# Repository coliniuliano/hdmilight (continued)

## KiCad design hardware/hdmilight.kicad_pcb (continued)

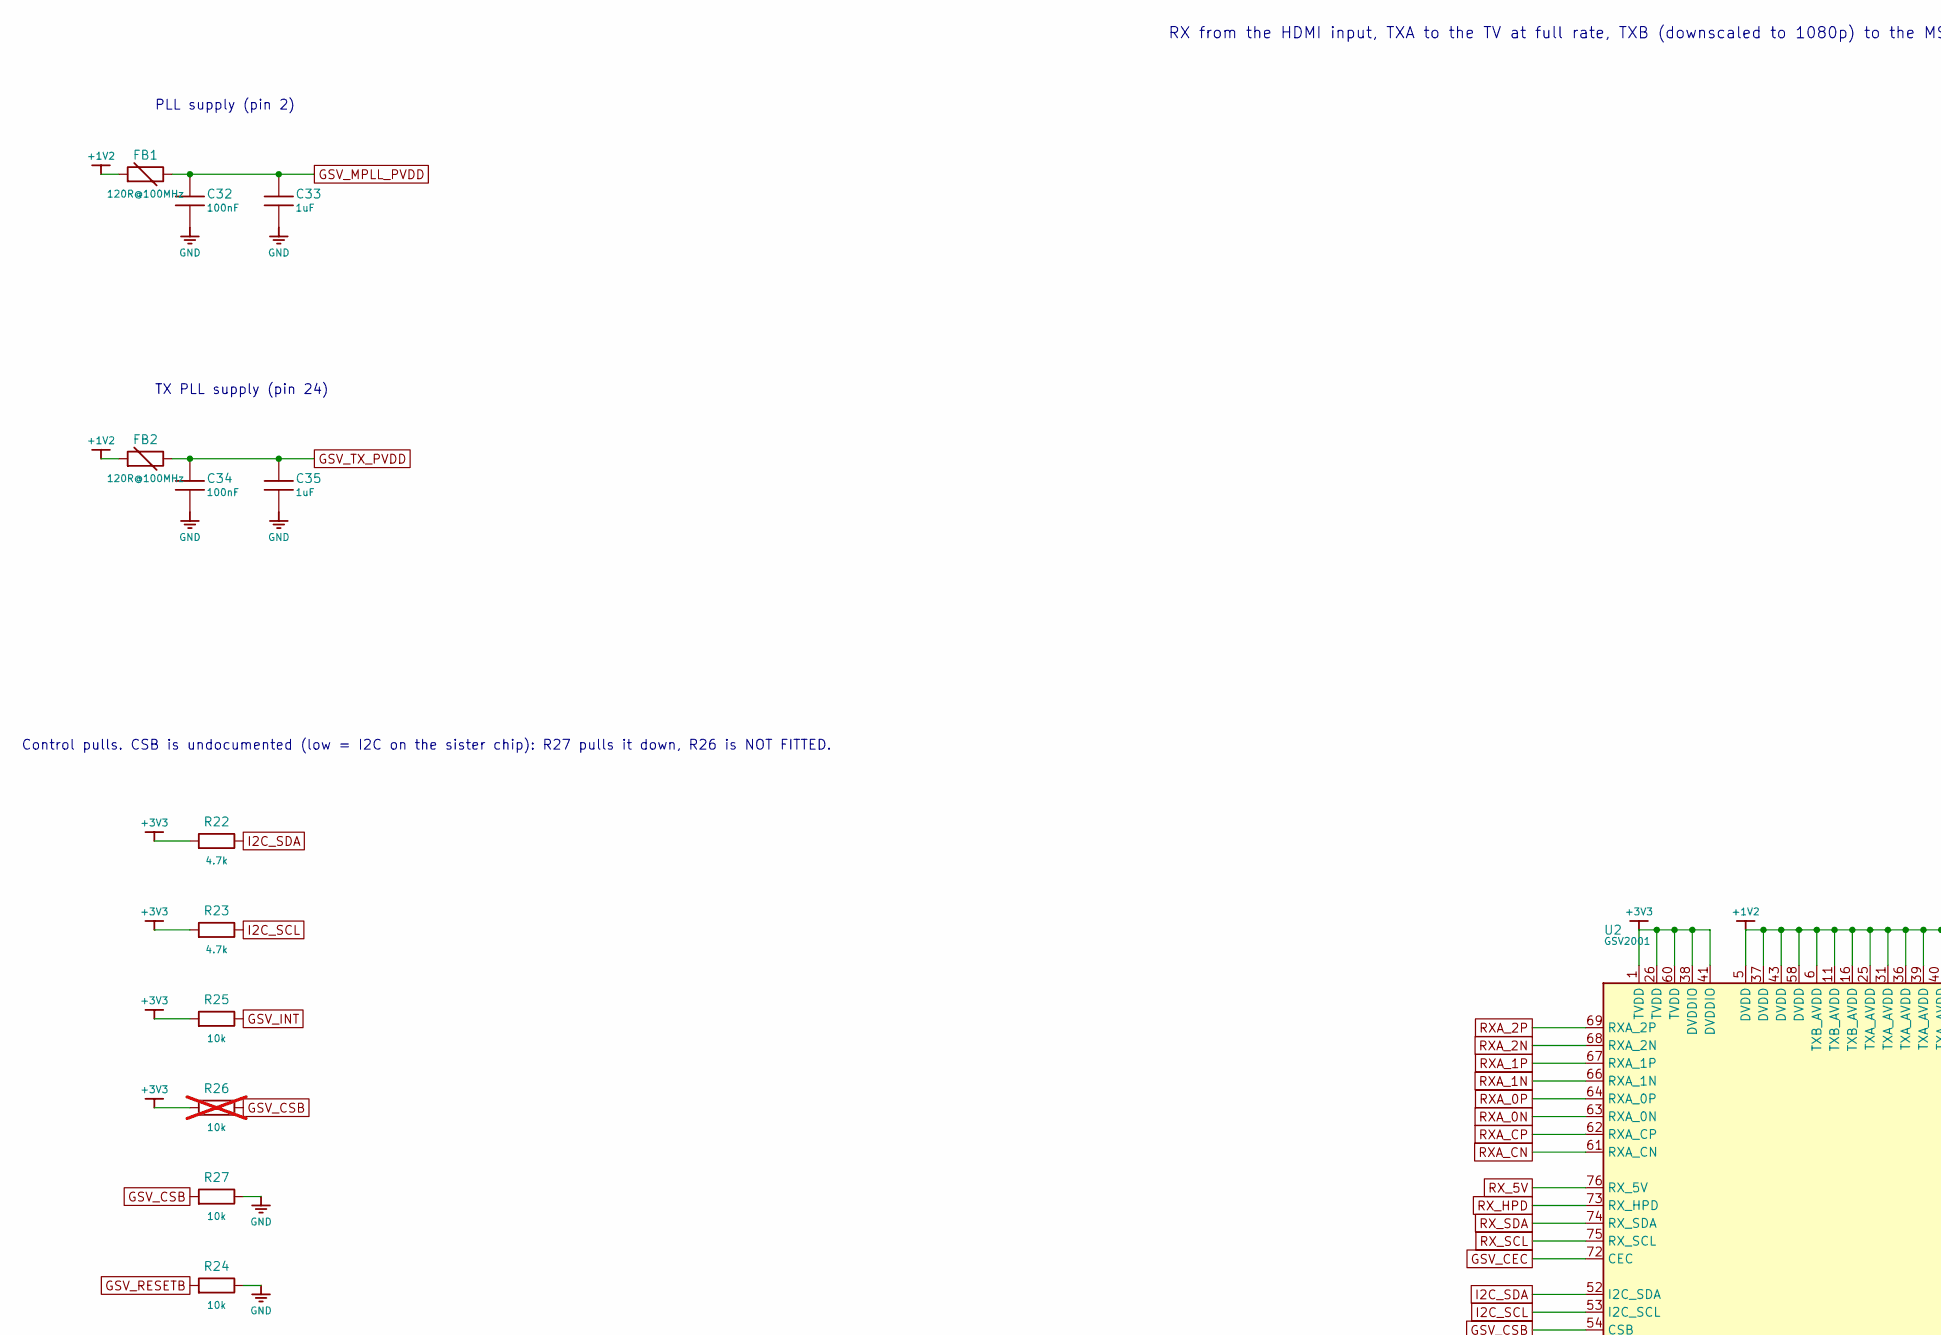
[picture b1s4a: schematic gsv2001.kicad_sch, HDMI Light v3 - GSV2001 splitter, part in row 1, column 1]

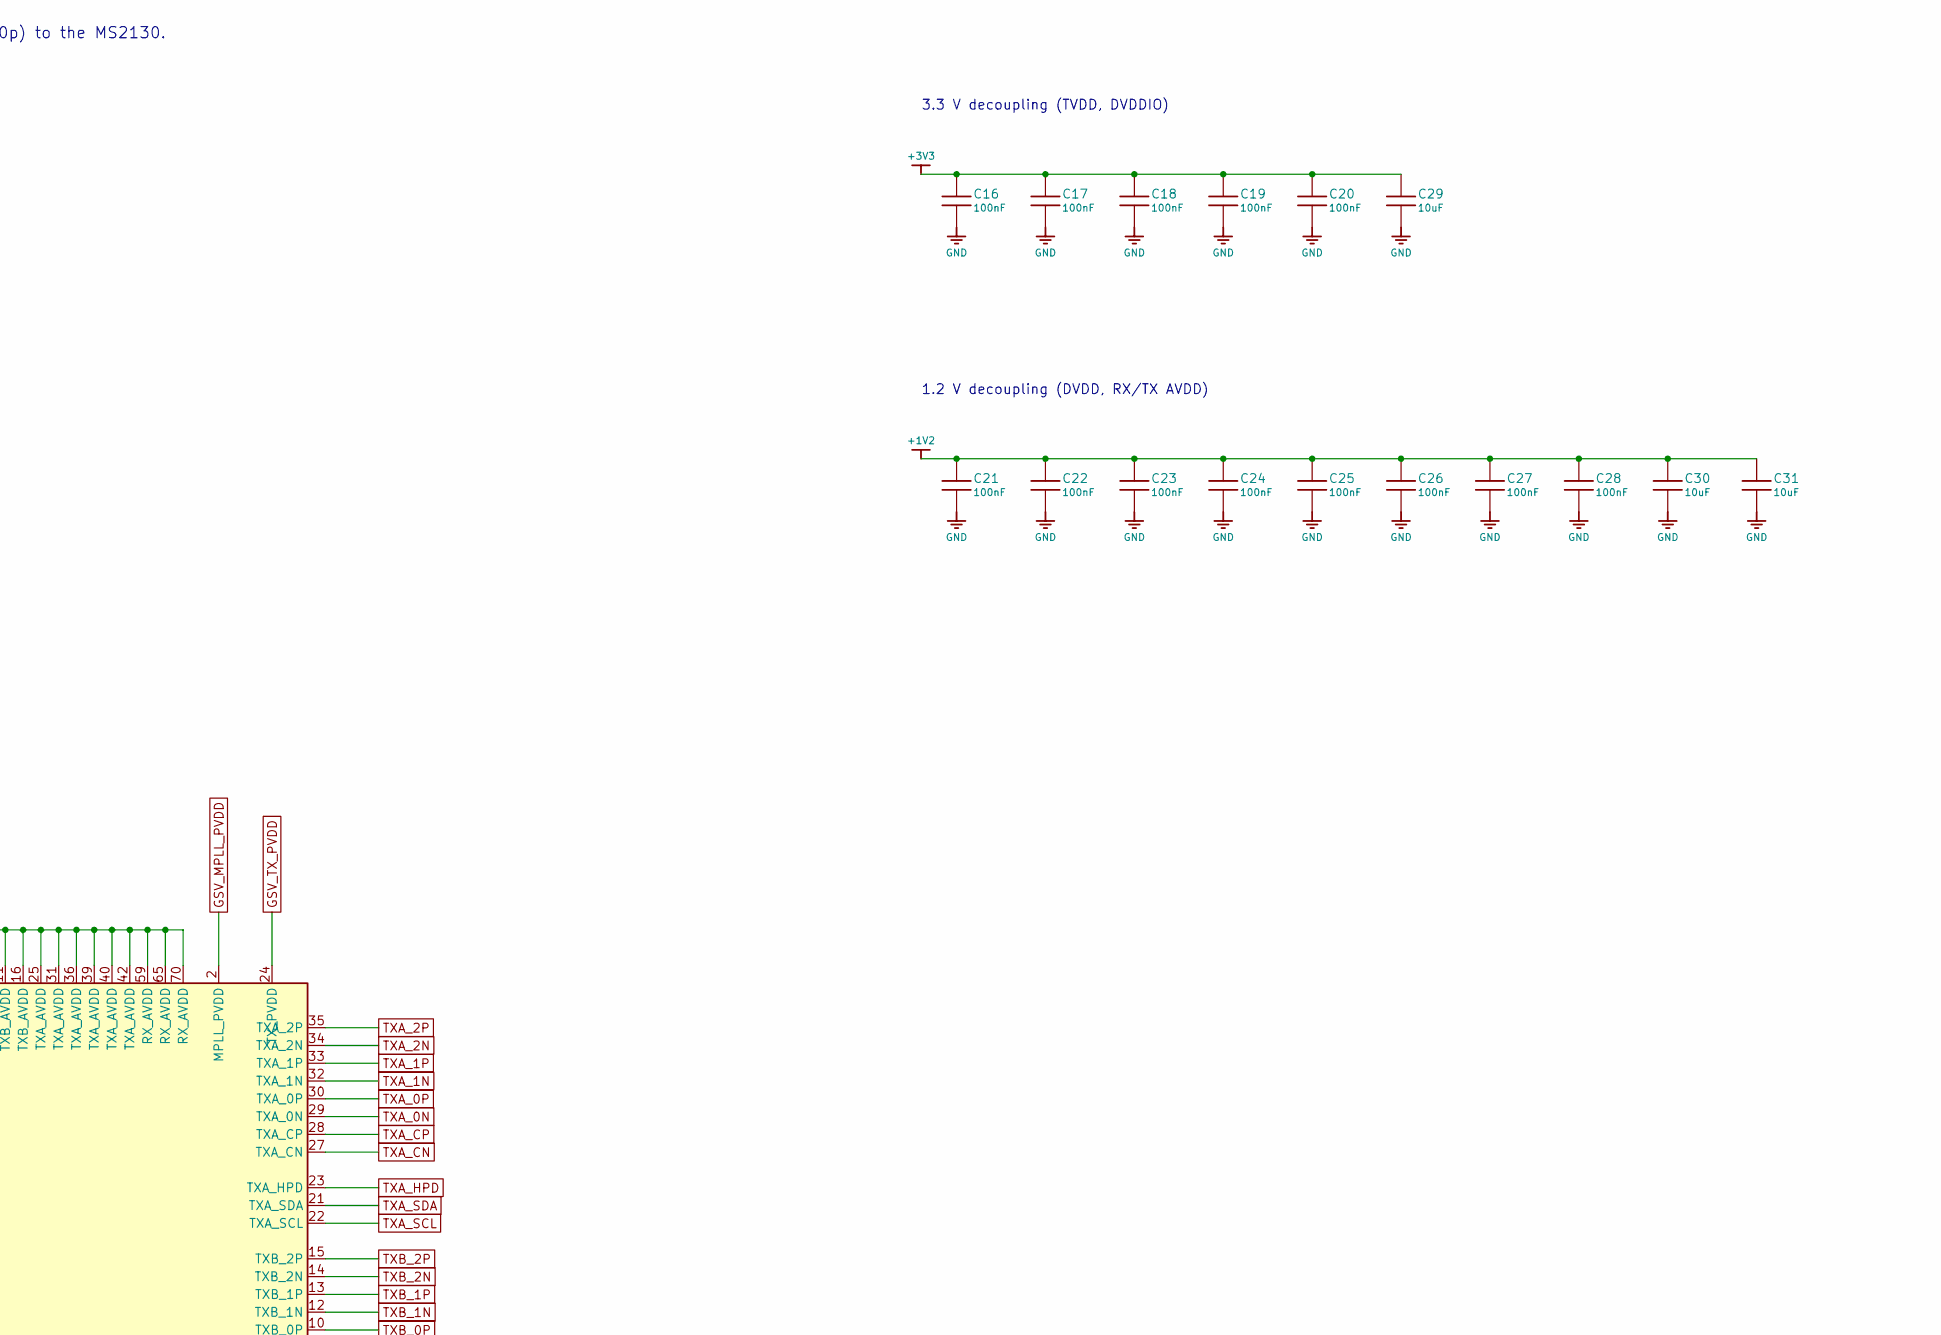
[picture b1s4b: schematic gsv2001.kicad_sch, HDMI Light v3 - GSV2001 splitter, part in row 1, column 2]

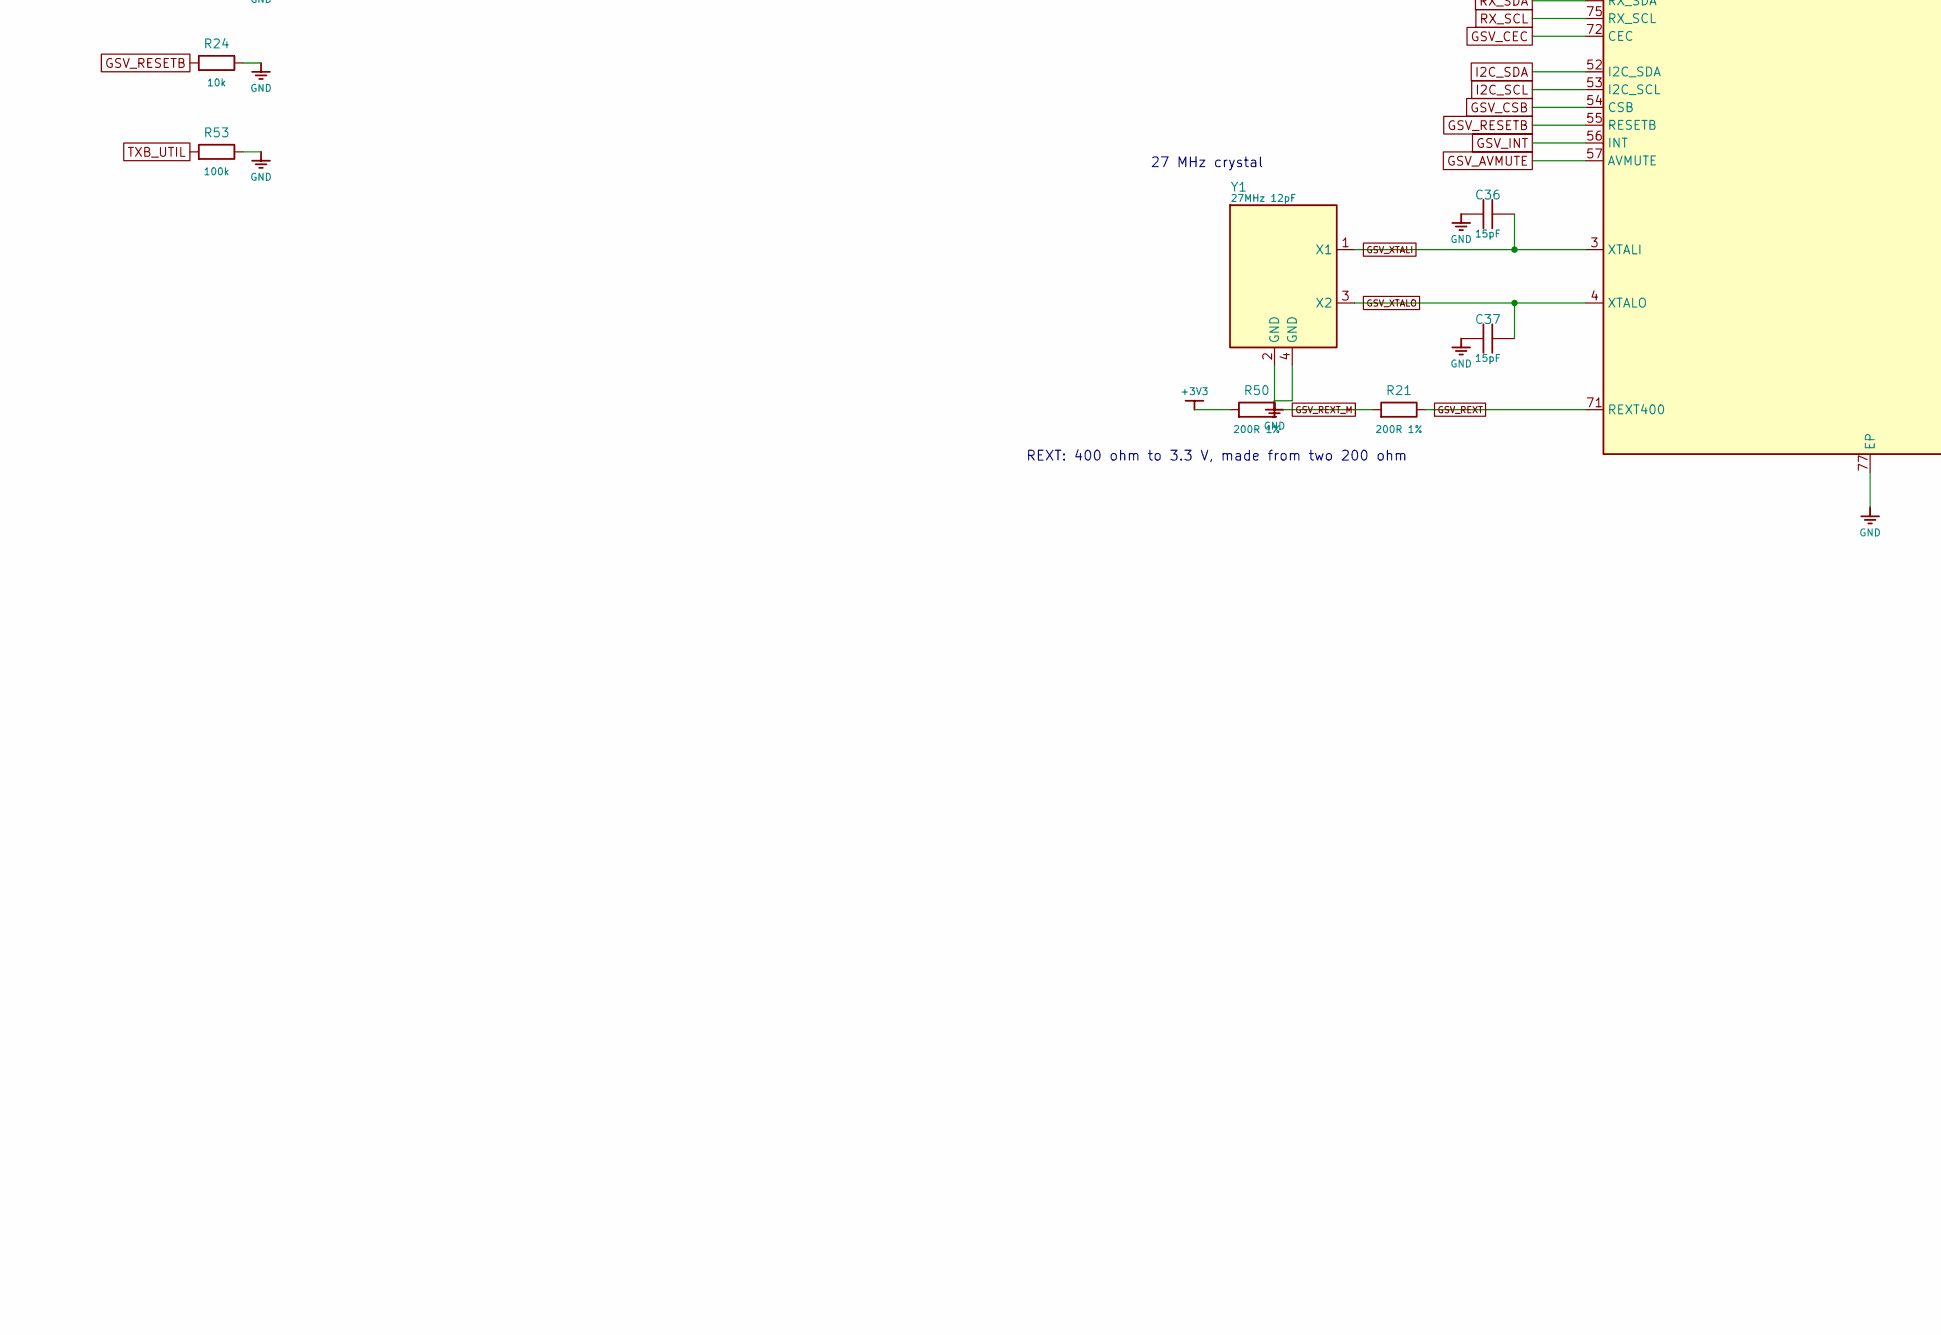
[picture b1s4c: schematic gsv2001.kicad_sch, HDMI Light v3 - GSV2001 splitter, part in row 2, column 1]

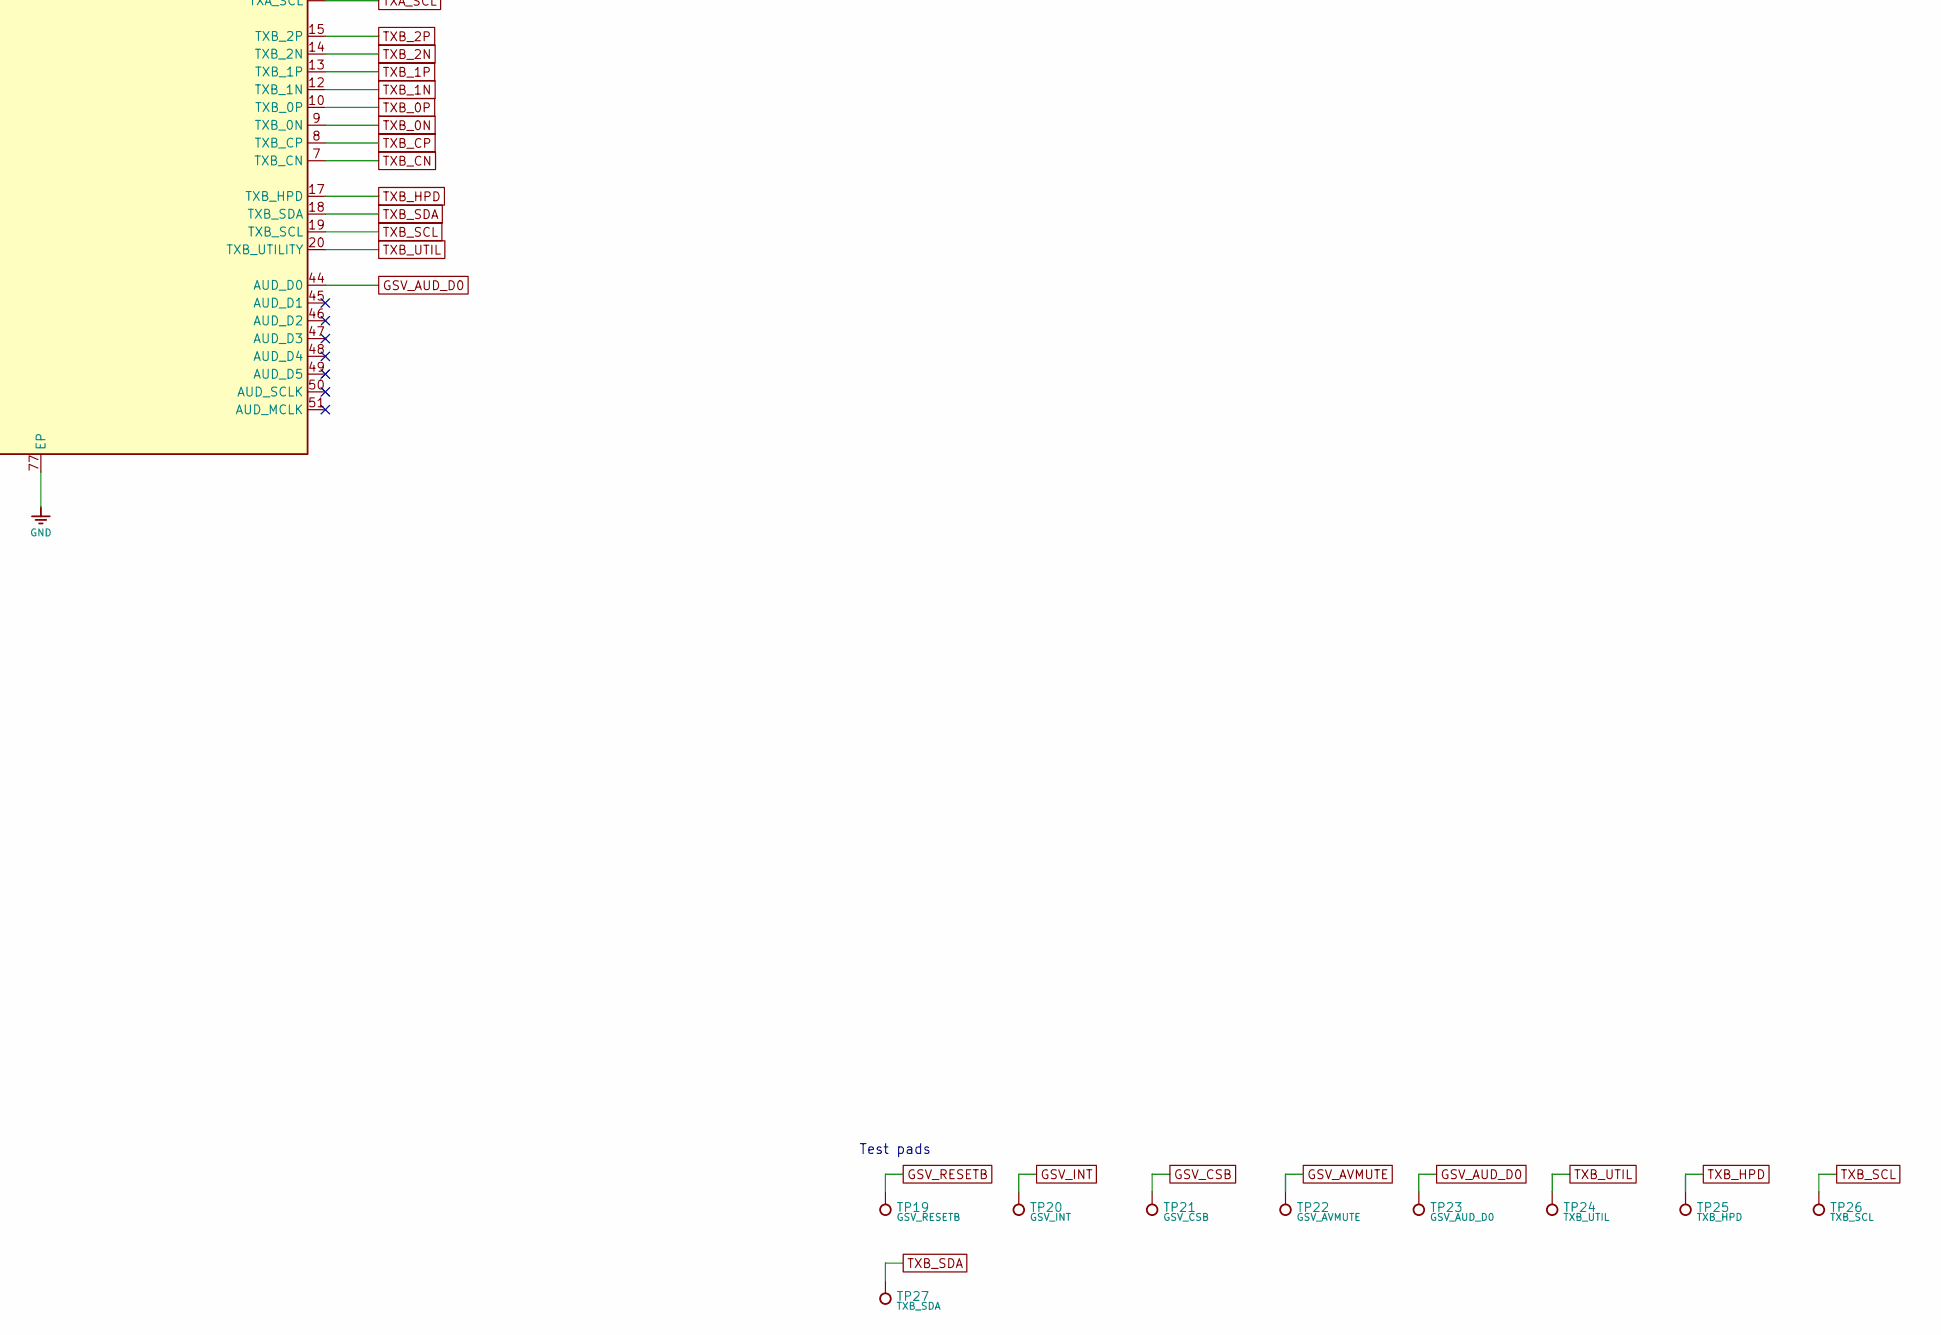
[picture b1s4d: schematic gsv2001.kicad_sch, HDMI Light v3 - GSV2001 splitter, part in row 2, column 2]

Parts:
C16, C17, C18, C19, C20, C21, C22, C23, C24, C25, C26, C27, C28, C32, C34: 100nF; C_0402_1005Metric; LCSC C1525
C29, C30, C31: 10uF; C_0603_1608Metric; LCSC C19702
C33, C35: 1uF; C_0603_1608Metric; LCSC C15849
C36, C37: 15pF; C_0402_1005Metric; LCSC C1548
FB1, FB2: 120R@100MHz; L_0603_1608Metric; MPN BLM18PG121SN1D; LCSC C14709
R21, R50: 200R 1%; R_0603_1608Metric; LCSC C8218
R22, R23: 4.7k; R_0603_1608Metric; LCSC C23162
R24, R25, R27: 10k; R_0603_1608Metric; LCSC C25804
R26: 10k; R_0603_1608Metric; LCSC C25804; not fitted
R53: 100k; R_0603_1608Metric; LCSC C25803
TP19: GSV_RESETB; TestPoint_Pad_D1.0mm
TP20: GSV_INT; TestPoint_Pad_D1.0mm
TP21: GSV_CSB; TestPoint_Pad_D1.0mm
TP22: GSV_AVMUTE; TestPoint_Pad_D1.0mm
TP23: GSV_AUD_D0; TestPoint_Pad_D1.0mm
TP24: TXB_UTIL; TestPoint_Pad_D1.0mm
TP25: TXB_HPD; TestPoint_Pad_D1.0mm
TP26: TXB_SCL; TestPoint_Pad_D1.0mm
TP27: TXB_SDA; TestPoint_Pad_D1.0mm
U2: GSV2001; QFN-76-1EP_9x9mm_P0.4mm_EP6.3x6.3mm; MPN GSV2001
Y1: 27MHz 12pF; Crystal_SMD_3225-4Pin_3.2x2.5mm; MPN X322527MOB4SI; LCSC C70595

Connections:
+1V2: C21.1, C22.1, C23.1, C24.1, C25.1, C26.1, C27.1, C28.1, C30.1, C31.1, FB1.1, FB2.1, U2.5 (DVDD), U2.6 (TXB_AVDD), U2.11 (TXB_AVDD), U2.16 (TXB_AVDD), U2.25 (TXA_AVDD), U2.31 (TXA_AVDD), U2.36 (TXA_AVDD), U2.37 (DVDD), U2.39 (TXA_AVDD), U2.40 (TXA_AVDD), U2.42 (TXA_AVDD), U2.43 (DVDD), U2.58 (DVDD), U2.59 (RX_AVDD), U2.65 (RX_AVDD), U2.70 (RX_AVDD); also elsewhere on the board
+3V3: C16.1, C17.1, C18.1, C19.1, C20.1, C29.1, R22.1, R23.1, R25.1, R26.1, R50.1, U2.1 (TVDD), U2.26 (TVDD), U2.38 (DVDDIO), U2.41 (DVDDIO), U2.60 (TVDD); also elsewhere on the board
GND: C16.2, C17.2, C18.2, C19.2, C20.2, C21.2, C22.2, C23.2, C24.2, C25.2, C26.2, C27.2, C28.2, C29.2, C30.2, C31.2, C32.2, C33.2, C34.2, C35.2, C36.2, C37.2, R24.2, R27.2, R53.2, U2.77 (EP), Y1.2 (GND), Y1.4 (GND); also elsewhere on the board
GSV_AUD_D0: TP23.1, U2.44 (AUD_D0)
GSV_AVMUTE: TP22.1, U2.57 (AVMUTE)
GSV_CEC: U2.72 (CEC); also elsewhere on the board
GSV_CSB: R26.2, R27.1, TP21.1, U2.54 (CSB); also elsewhere on the board
GSV_INT: R25.2, TP20.1, U2.56 (INT); also elsewhere on the board
GSV_MPLL_PVDD: C32.1, C33.1, FB1.2, U2.2 (MPLL_PVDD)
GSV_RESETB: R24.1, TP19.1, U2.55 (RESETB); also elsewhere on the board
GSV_REXT: R21.2, U2.71 (REXT400)
GSV_REXT_M: R21.1, R50.2
GSV_TX_PVDD: C34.1, C35.1, FB2.2, U2.24 (TX_PVDD)
GSV_XTALI: C36.1, U2.3 (XTALI), Y1.1 (X1)
GSV_XTALO: C37.1, U2.4 (XTALO), Y1.3 (X2)
I2C_SCL: R23.2, U2.53 (I2C_SCL); also elsewhere on the board
I2C_SDA: R22.2, U2.52 (I2C_SDA); also elsewhere on the board
RXA_0N: U2.63 (RXA_0N); also elsewhere on the board
RXA_0P: U2.64 (RXA_0P); also elsewhere on the board
RXA_1N: U2.66 (RXA_1N); also elsewhere on the board
RXA_1P: U2.67 (RXA_1P); also elsewhere on the board
RXA_2N: U2.68 (RXA_2N); also elsewhere on the board
RXA_2P: U2.69 (RXA_2P); also elsewhere on the board
RXA_CN: U2.61 (RXA_CN); also elsewhere on the board
RXA_CP: U2.62 (RXA_CP); also elsewhere on the board
RX_5V: U2.76 (RX_5V); also elsewhere on the board
RX_HPD: U2.73 (RX_HPD); also elsewhere on the board
RX_SCL: U2.75 (RX_SCL); also elsewhere on the board
RX_SDA: U2.74 (RX_SDA); also elsewhere on the board
TXA_0N: U2.29 (TXA_0N); also elsewhere on the board
TXA_0P: U2.30 (TXA_0P); also elsewhere on the board
TXA_1N: U2.32 (TXA_1N); also elsewhere on the board
TXA_1P: U2.33 (TXA_1P); also elsewhere on the board
TXA_2N: U2.34 (TXA_2N); also elsewhere on the board
TXA_2P: U2.35 (TXA_2P); also elsewhere on the board
TXA_CN: U2.27 (TXA_CN); also elsewhere on the board
TXA_CP: U2.28 (TXA_CP); also elsewhere on the board
TXA_HPD: U2.23 (TXA_HPD); also elsewhere on the board
TXA_SCL: U2.22 (TXA_SCL); also elsewhere on the board
TXA_SDA: U2.21 (TXA_SDA); also elsewhere on the board
TXB_0N: U2.9 (TXB_0N); also elsewhere on the board
TXB_0P: U2.10 (TXB_0P); also elsewhere on the board
TXB_1N: U2.12 (TXB_1N); also elsewhere on the board
TXB_1P: U2.13 (TXB_1P); also elsewhere on the board
TXB_2N: U2.14 (TXB_2N); also elsewhere on the board
TXB_2P: U2.15 (TXB_2P); also elsewhere on the board
TXB_CN: U2.7 (TXB_CN); also elsewhere on the board
TXB_CP: U2.8 (TXB_CP); also elsewhere on the board
TXB_HPD: TP25.1, U2.17 (TXB_HPD); also elsewhere on the board
TXB_SCL: TP26.1, U2.19 (TXB_SCL); also elsewhere on the board
TXB_SDA: TP27.1, U2.18 (TXB_SDA); also elsewhere on the board
TXB_UTIL: R53.1, TP24.1, U2.20 (TXB_UTILITY)

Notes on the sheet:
27 MHz crystal
REXT: 400 ohm to 3.3 V, made from two 200 ohm
PLL supply (pin 2)
TX PLL supply (pin 24)
3.3 V decoupling (TVDD, DVDDIO)
1.2 V decoupling (DVDD, RX/TX AVDD)
Control pulls. CSB is undocumented (low = I2C on the sister chip): R27 pulls it down, R26 is NOT FITTED.
Test pads
RX from the HDMI input, TXA to the TV at full rate, TXB (downscaled to 1080p) to the MS2130.

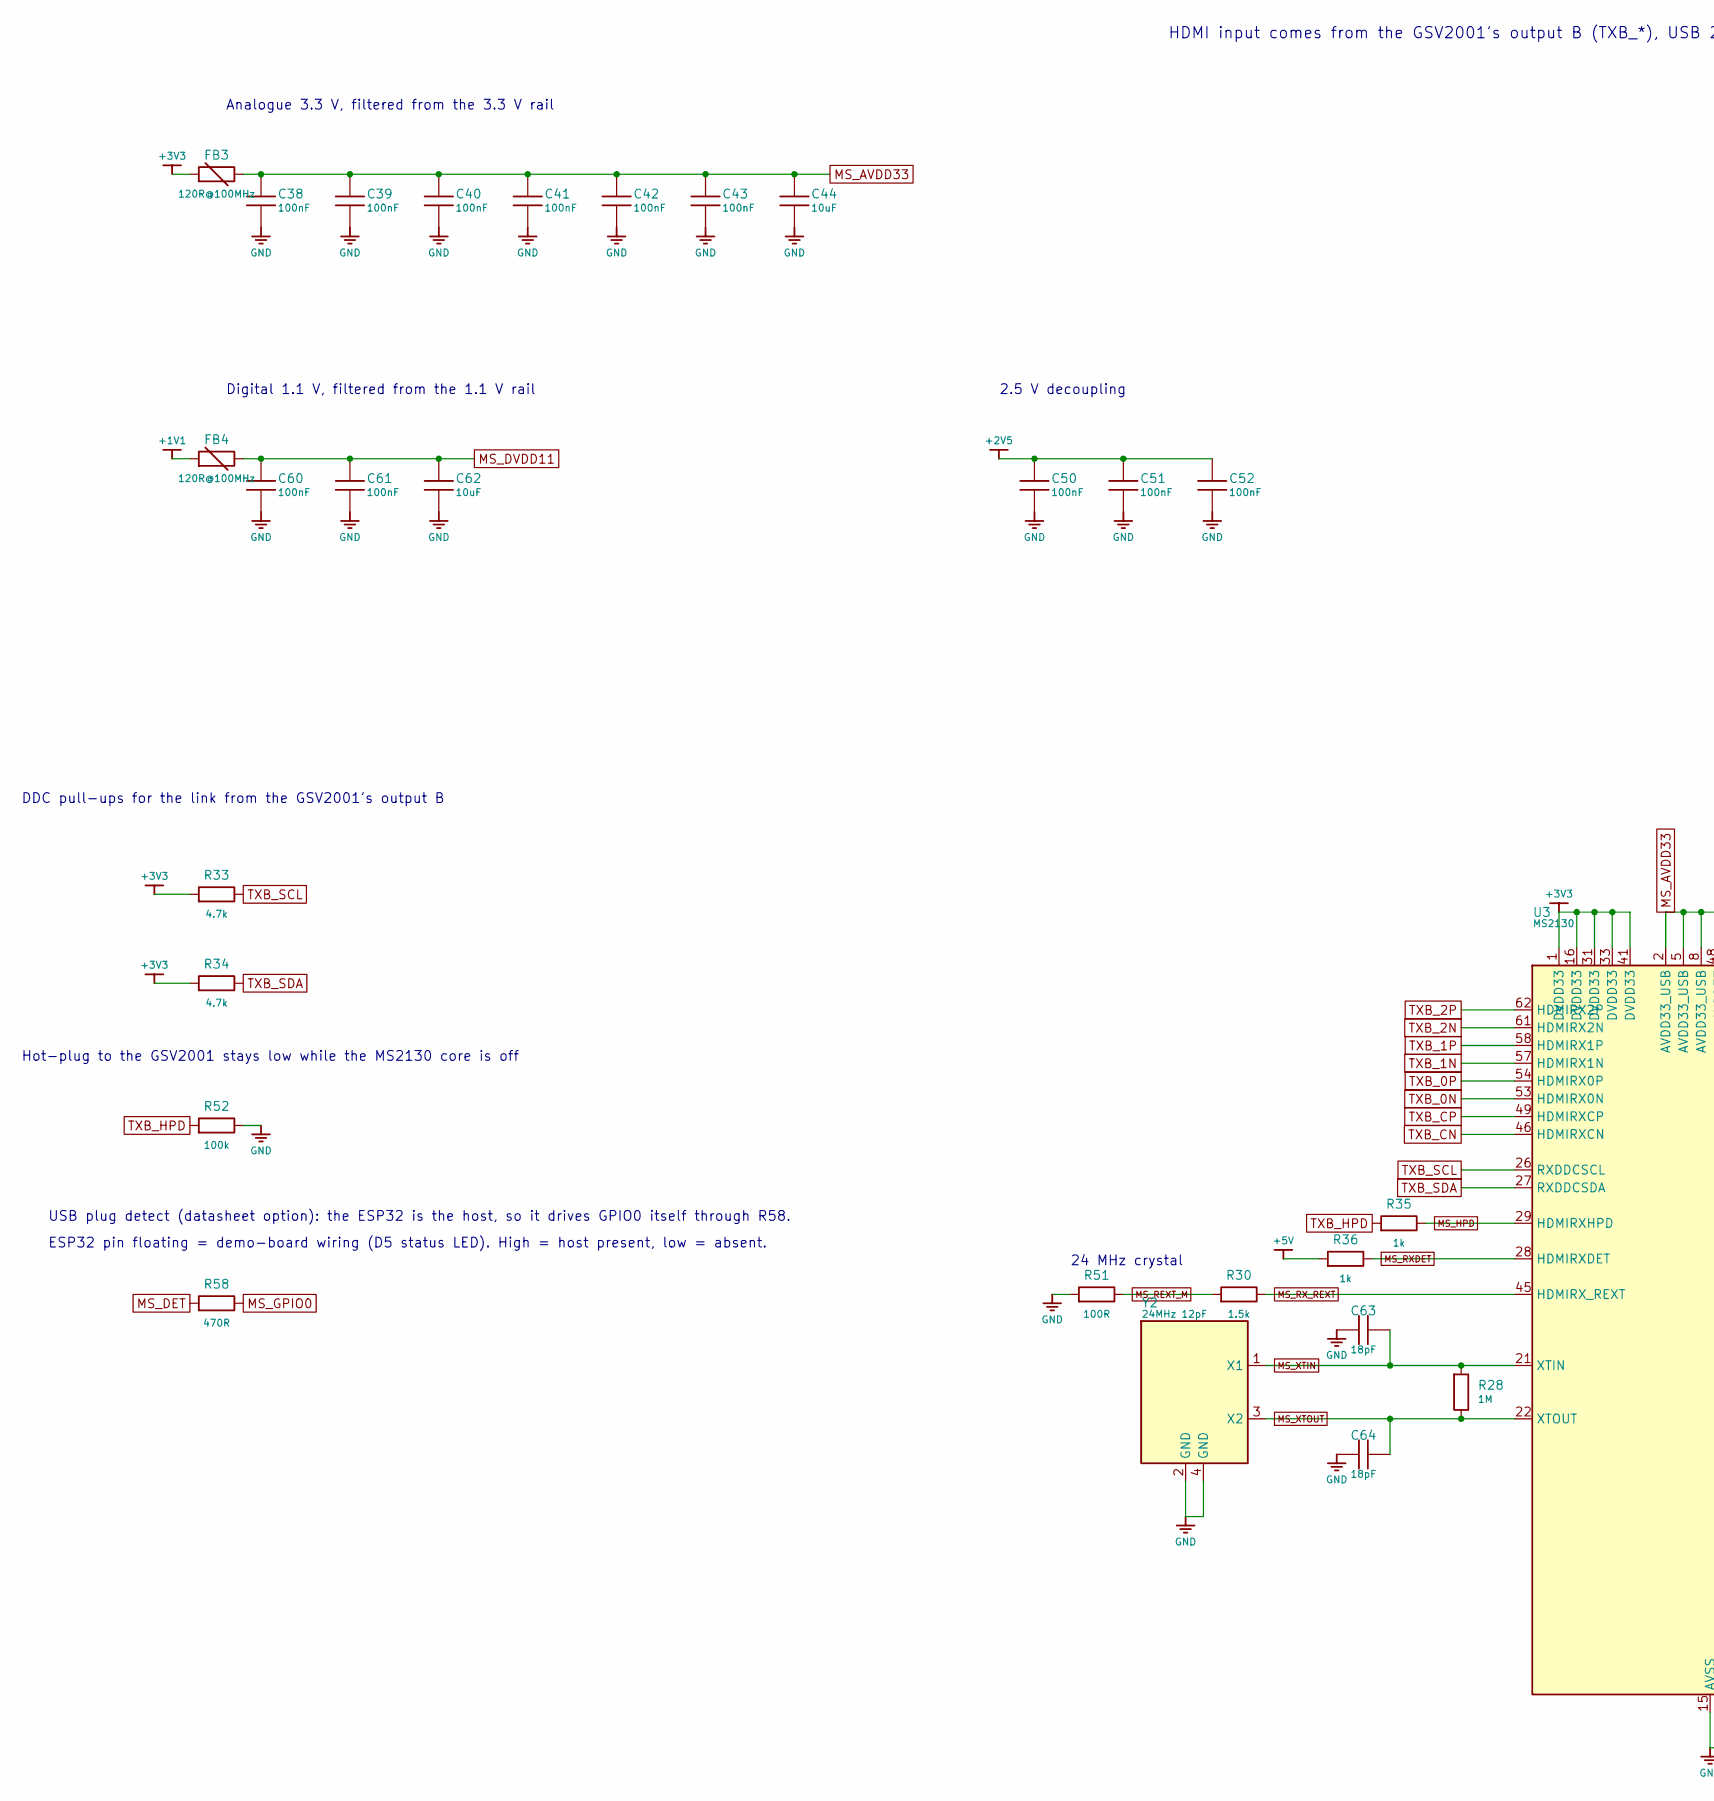
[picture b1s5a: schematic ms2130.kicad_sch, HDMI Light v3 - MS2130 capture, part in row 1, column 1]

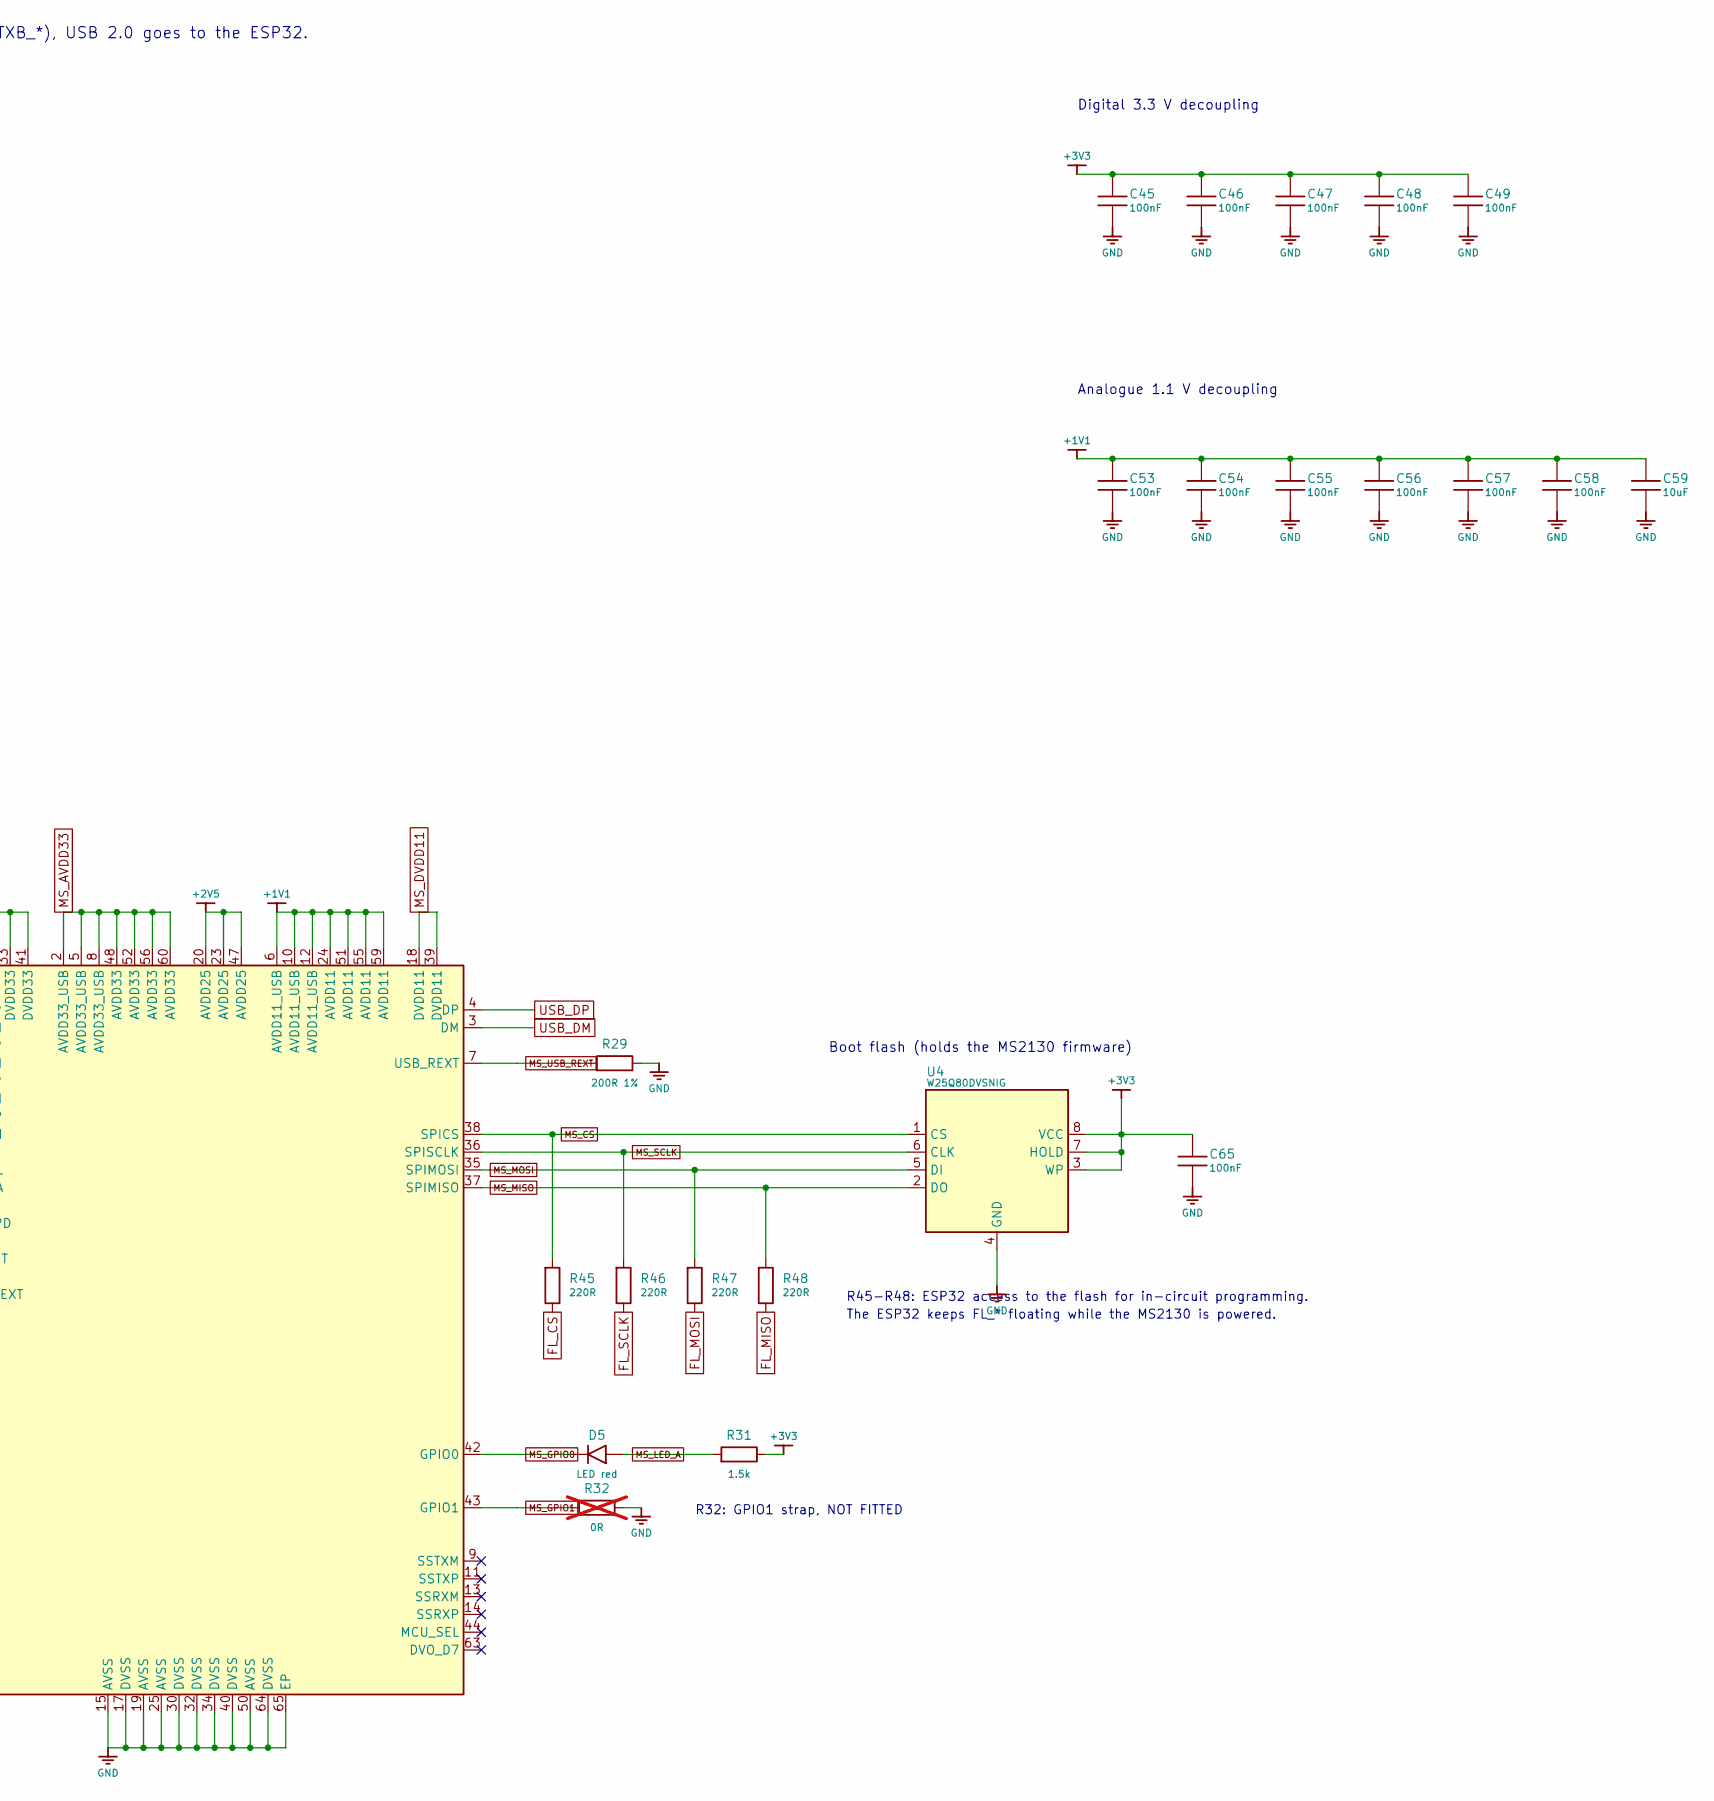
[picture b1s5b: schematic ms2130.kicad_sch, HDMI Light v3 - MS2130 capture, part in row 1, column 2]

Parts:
C38, C39, C40, C41, C42, C43, C45, C46, C47, C48, C49, C50, C51, C52, C53, C54, C55, C56, C57, C58, C60, C61, C65: 100nF; C_0402_1005Metric; LCSC C1525
C44, C59, C62: 10uF; C_0603_1608Metric; LCSC C19702
C63, C64: 18pF; C_0402_1005Metric; LCSC C1549
D5: LED red; LED_0603_1608Metric; LCSC C2286
FB3, FB4: 120R@100MHz; L_0603_1608Metric; MPN BLM18PG121SN1D; LCSC C14709
R28: 1M; R_0603_1608Metric; LCSC C22935
R29: 200R 1%; R_0603_1608Metric; LCSC C8218
R30, R31: 1.5k; R_0603_1608Metric; LCSC C22843
R32: 0R; R_0603_1608Metric; LCSC C21189; not fitted
R33, R34: 4.7k; R_0603_1608Metric; LCSC C23162
R35, R36: 1k; R_0603_1608Metric; LCSC C21190
R45, R46, R47, R48: 220R; R_0603_1608Metric; LCSC C22962
R51: 100R; R_0603_1608Metric; LCSC C22775
R52: 100k; R_0603_1608Metric; LCSC C25803
R58: 470R; R_0603_1608Metric; LCSC C23179
U3: MS2130; QFN-64-1EP_9x9mm_P0.5mm_EP5.7x5.7mm; MPN MS2130; LCSC C5905137
U4: W25Q80DVSNIG; SOIC-8_3.9x4.9mm_P1.27mm; MPN W25Q80DVSNIG; LCSC C401655
Y2: 24MHz 12pF; Crystal_SMD_3225-4Pin_3.2x2.5mm; MPN X322524MOB4SI; LCSC C70590

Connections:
+1V1: C53.1, C54.1, C55.1, C56.1, C57.1, C58.1, C59.1, FB4.1, U3.6 (AVDD11_USB), U3.10 (AVDD11_USB), U3.12 (AVDD11_USB), U3.24 (AVDD11), U3.51 (AVDD11), U3.55 (AVDD11), U3.59 (AVDD11); also elsewhere on the board
+2V5: C50.1, C51.1, C52.1, U3.20 (AVDD25), U3.23 (AVDD25), U3.47 (AVDD25); also elsewhere on the board
+3V3: C45.1, C46.1, C47.1, C48.1, C49.1, C65.1, FB3.1, R31.1, R33.1, R34.1, U3.1 (DVDD33), U3.16 (DVDD33), U3.31 (DVDD33), U3.33 (DVDD33), U3.41 (DVDD33), U4.3 (WP), U4.7 (HOLD), U4.8 (VCC); also elsewhere on the board
+5V: R36.1; also elsewhere on the board
FL_CS: R45.2; also elsewhere on the board
FL_MISO: R48.2; also elsewhere on the board
FL_MOSI: R47.2; also elsewhere on the board
FL_SCLK: R46.2; also elsewhere on the board
GND: C38.2, C39.2, C40.2, C41.2, C42.2, C43.2, C44.2, C45.2, C46.2, C47.2, C48.2, C49.2, C50.2, C51.2, C52.2, C53.2, C54.2, C55.2, C56.2, C57.2, C58.2, C59.2, C60.2, C61.2, C62.2, C63.2, C64.2, C65.2, R29.2, R32.2, R51.2, R52.2, U3.15 (AVSS), U3.17 (DVSS), U3.19 (AVSS), U3.25 (AVSS), U3.30 (DVSS), U3.32 (DVSS), U3.34 (DVSS), U3.40 (DVSS), U3.50 (AVSS), U3.64 (DVSS), U3.65 (EP), U4.4 (GND), Y2.2 (GND), Y2.4 (GND); also elsewhere on the board
MS_AVDD33: C38.1, C39.1, C40.1, C41.1, C42.1, C43.1, C44.1, FB3.2, U3.2 (AVDD33_USB), U3.5 (AVDD33_USB), U3.8 (AVDD33_USB), U3.48 (AVDD33), U3.52 (AVDD33), U3.56 (AVDD33), U3.60 (AVDD33)
MS_CS: R45.1, U3.38 (SPICS), U4.1 (CS)
MS_DET: R58.1; also elsewhere on the board
MS_DVDD11: C60.1, C61.1, C62.1, FB4.2, U3.18 (DVDD11), U3.39 (DVDD11)
MS_GPIO0: D5.1, R58.2, U3.42 (GPIO0)
MS_GPIO1: R32.1, U3.43 (GPIO1)
MS_HPD: R35.1, U3.29 (HDMIRXHPD)
MS_LED_A: D5.2, R31.2
MS_MISO: R48.1, U3.37 (SPIMISO), U4.2 (DO)
MS_MOSI: R47.1, U3.35 (SPIMOSI), U4.5 (DI)
MS_REXT_M: R30.2, R51.1
MS_RXDET: R36.2, U3.28 (HDMIRXDET)
MS_RX_REXT: R30.1, U3.45 (HDMIRX_REXT)
MS_SCLK: R46.1, U3.36 (SPISCLK), U4.6 (CLK)
MS_USB_REXT: R29.1, U3.7 (USB_REXT)
MS_XTIN: C63.1, R28.1, U3.21 (XTIN), Y2.1 (X1)
MS_XTOUT: C64.1, R28.2, U3.22 (XTOUT), Y2.3 (X2)
TXB_0N: U3.53 (HDMIRX0N); also elsewhere on the board
TXB_0P: U3.54 (HDMIRX0P); also elsewhere on the board
TXB_1N: U3.57 (HDMIRX1N); also elsewhere on the board
TXB_1P: U3.58 (HDMIRX1P); also elsewhere on the board
TXB_2N: U3.61 (HDMIRX2N); also elsewhere on the board
TXB_2P: U3.62 (HDMIRX2P); also elsewhere on the board
TXB_CN: U3.46 (HDMIRXCN); also elsewhere on the board
TXB_CP: U3.49 (HDMIRXCP); also elsewhere on the board
TXB_HPD: R35.2, R52.1; also elsewhere on the board
TXB_SCL: R33.2, U3.26 (RXDDCSCL); also elsewhere on the board
TXB_SDA: R34.2, U3.27 (RXDDCSDA); also elsewhere on the board
USB_DM: U3.3 (DM); also elsewhere on the board
USB_DP: U3.4 (DP); also elsewhere on the board

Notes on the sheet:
24 MHz crystal
Boot flash (holds the MS2130 firmware)
R45-R48: ESP32 access to the flash for in-circuit programming.
The ESP32 keeps FL_* floating while the MS2130 is powered.
R32: GPIO1 strap, NOT FITTED
Analogue 3.3 V, filtered from the 3.3 V rail
Digital 1.1 V, filtered from the 1.1 V rail
Digital 3.3 V decoupling
Analogue 1.1 V decoupling
2.5 V decoupling
DDC pull-ups for the link from the GSV2001's output B
Hot-plug to the GSV2001 stays low while the MS2130 core is off
USB plug detect (datasheet option): the ESP32 is the host, so it drives GPIO0 itself through R58.
ESP32 pin floating = demo-board wiring (D5 status LED). High = host present, low = absent.
HDMI input comes from the GSV2001's output B (TXB_*), USB 2.0 goes to the ESP32.
